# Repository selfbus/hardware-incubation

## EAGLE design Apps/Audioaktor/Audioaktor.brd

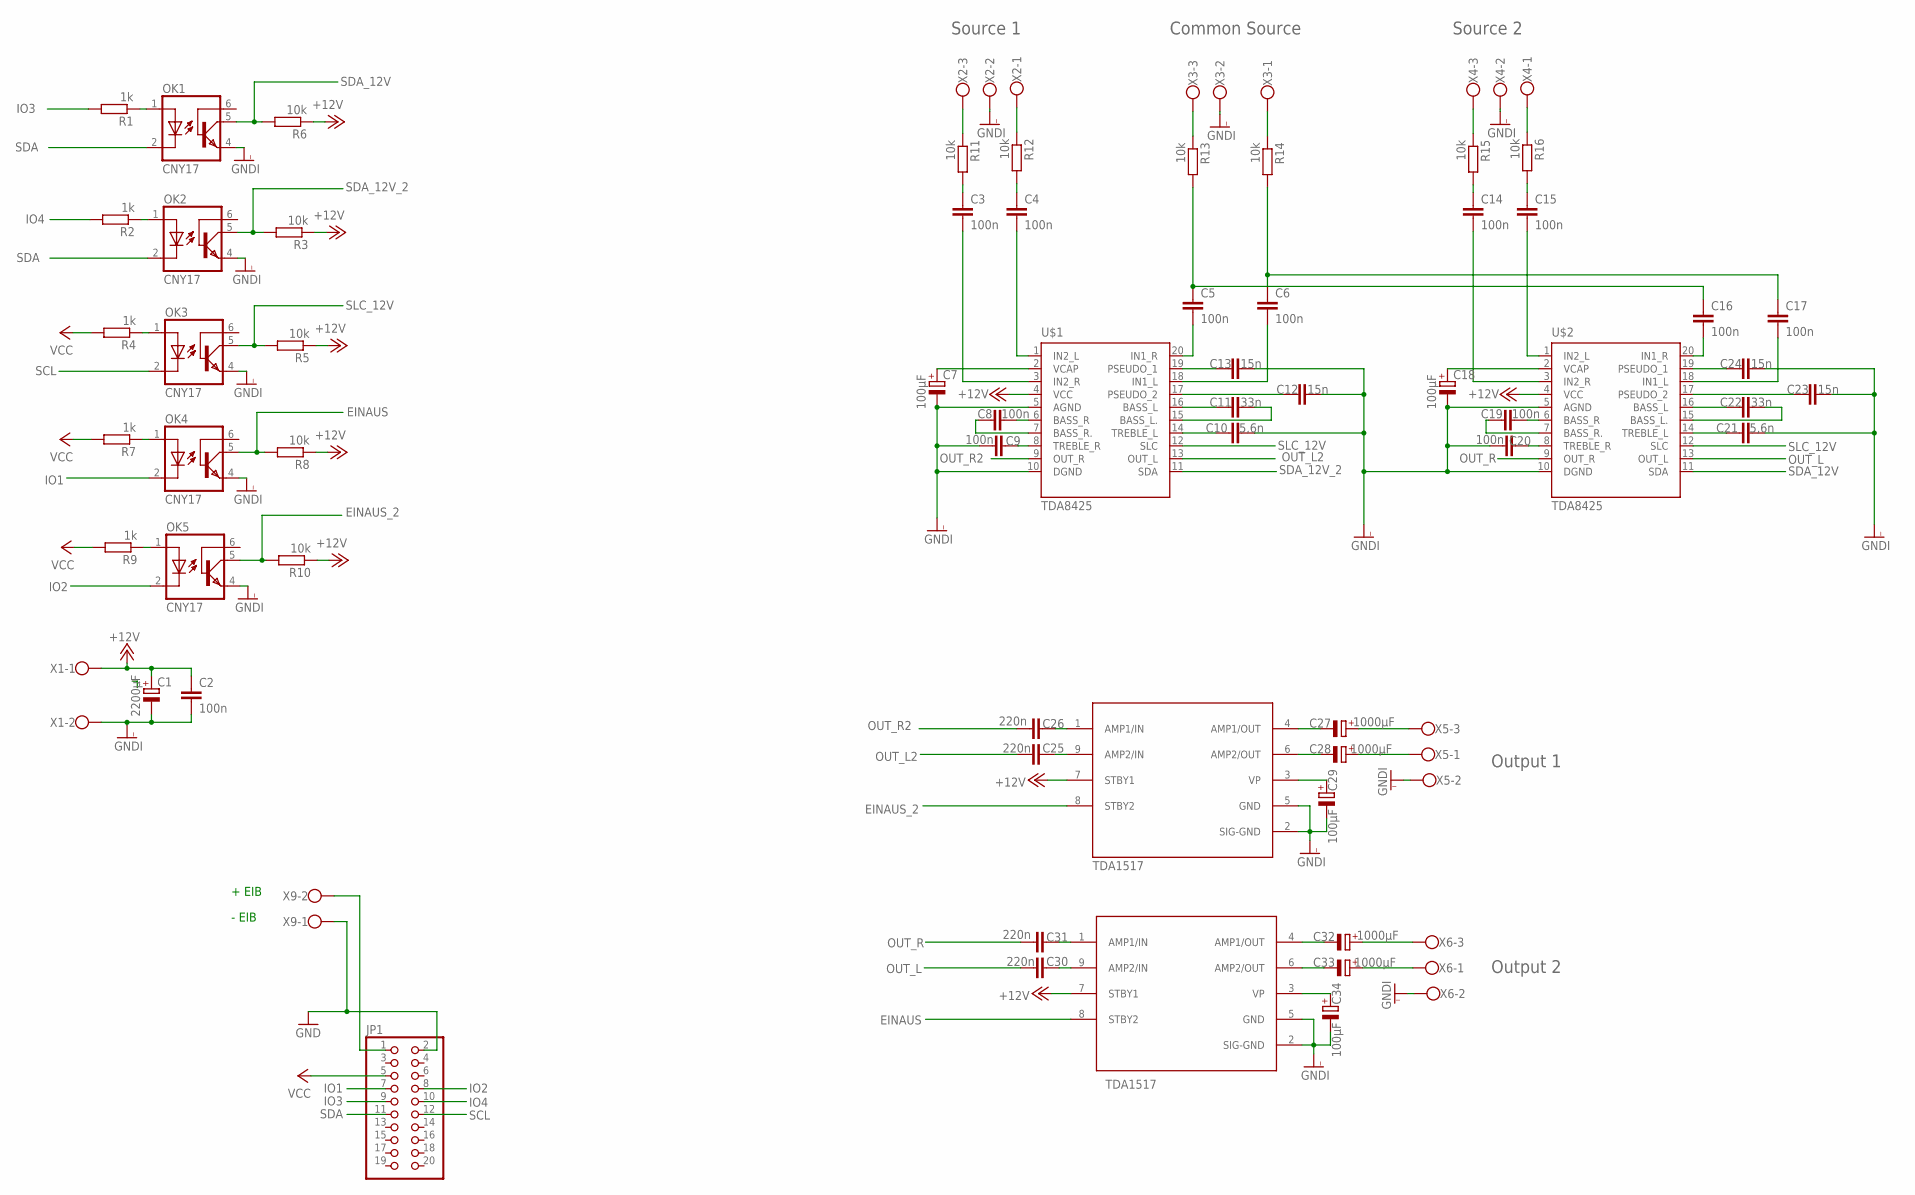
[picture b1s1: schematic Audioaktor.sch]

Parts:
C1: 2200µF; E5-10,5
C2, C3, C4, C5, C6, C8, C9, C14, C15, C16, C17, C19, C20: 100n; C050-030X075
C7, C18, C29, C34: 100µF; E5-10,5
C10, C21: 5,6n; C050-030X075
C11, C22: 33n; C050-030X075
C12, C13, C23, C24: 15n; C050-030X075
C25, C26, C30, C31: 220n; C050-030X075
C27, C28, C32, C33: 1000µF; E5-10,5
JP1: PINHD-2X10; 2X10
OK1, OK2, OK3, OK4, OK5: CNY17; DIL06
R1, R2, R4, R7, R9: 1k; 0204/7
R3, R5, R6, R8, R10, R11, R12, R13, R14, R15, R16: 10k; 0204/7
TDA1517: TDA1517
U$1, U$2: TDA8425; DIL20
U$3: TDA1517
X1, X9: W237-102
X2, X3, X4, X5, X6: W237-103

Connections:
+12V: C1.+, C2.1, R3.1, R5.1, R6.1, R8.1, R10.1, TDA1517.7 (STBY1), U$1.4 (VCC), U$2.4 (VCC), U$3.7 (STBY1), X1.1
EINAUS: OK4.5 (COL), R8.2, TDA1517.8 (STBY2)
EINAUS_2: OK5.5 (COL), R10.2, U$3.8 (STBY2)
GND: JP1.2, X9.1
GNDI: C1.-, C2.2, C7.-, C9.1, C10.2, C12.2, C13.2, C18.-, C20.1, C21.2, C23.2, C24.2, C29.-, C34.-, OK1.4 (EMI), OK2.4 (EMI), OK3.4 (EMI), OK4.4 (EMI), OK5.4 (EMI), TDA1517.2 (SIG-GND), TDA1517.5 (GND), U$1.5 (AGND), U$1.10 (DGND), U$2.5 (AGND), U$2.10 (DGND), U$3.2 (SIG-GND), U$3.5 (GND), X1.2, X2.2, X3.2, X4.2, X5.2, X6.2
IO1: JP1.7, OK4.2 (C)
IO2: JP1.8, OK5.2 (C)
IO3: JP1.9, R1.2
IO4: JP1.10, R2.2
unnamed: OK1.1 (A), R1.1
unnamed: OK2.1 (A), R2.1
unnamed: OK3.1 (A), R4.1
unnamed: OK4.1 (A), R7.1
unnamed: OK5.1 (A), R9.1
unnamed: R11.1, X2.3
unnamed: R12.1, X2.1
unnamed: C3.1, R11.2
unnamed: C4.1, R12.2
unnamed: R13.1, X3.3
unnamed: R14.1, X3.1
unnamed: C5.1, C16.1, R13.2
unnamed: C6.1, C17.1, R14.2
unnamed: C3.2, U$1.3 (IN2_R)
unnamed: C4.2, U$1.1 (IN2_L)
unnamed: C7.+, U$1.2 (VCAP)
unnamed: C8.2, U$1.6 (BASS_R)
unnamed: C8.1, U$1.7 (BASS_R.)
unnamed: JP1.1, X9.2
unnamed: C9.2, U$1.8 (TREBLE_R)
unnamed: C10.1, U$1.14 (TREBLE_L)
unnamed: C11.1, U$1.16 (BASS_L)
unnamed: C11.2, U$1.15 (BASS_L.)
unnamed: C13.1, U$1.19 (PSEUDO_1)
unnamed: C12.1, U$1.17 (PSEUDO_2)
unnamed: C5.2, U$1.20 (IN1_R)
unnamed: C6.2, U$1.18 (IN1_L)
unnamed: R15.1, X4.3
unnamed: R16.1, X4.1
unnamed: C14.1, R15.2
unnamed: C15.1, R16.2
unnamed: C26.2, U$3.1 (AMP1/IN)
unnamed: C25.2, U$3.9 (AMP2/IN)
unnamed: C27.-, U$3.4 (AMP1/OUT)
unnamed: C28.-, U$3.6 (AMP2/OUT)
unnamed: C14.2, U$2.3 (IN2_R)
unnamed: C15.2, U$2.1 (IN2_L)
unnamed: C18.+, U$2.2 (VCAP)
unnamed: C19.2, U$2.6 (BASS_R)
unnamed: C19.1, U$2.7 (BASS_R.)
unnamed: C20.2, U$2.8 (TREBLE_R)
unnamed: C21.1, U$2.14 (TREBLE_L)
unnamed: C22.1, U$2.16 (BASS_L)
unnamed: C22.2, U$2.15 (BASS_L.)
unnamed: C23.1, U$2.17 (PSEUDO_2)
unnamed: C24.1, U$2.19 (PSEUDO_1)
unnamed: C16.2, U$2.20 (IN1_R)
unnamed: C17.2, U$2.18 (IN1_L)
unnamed: C29.+, U$3.3 (VP)
unnamed: C31.2, TDA1517.1 (AMP1/IN)
unnamed: C27.+, X5.3
unnamed: C28.+, X5.1
unnamed: C30.2, TDA1517.9 (AMP2/IN)
unnamed: C32.-, TDA1517.4 (AMP1/OUT)
unnamed: C33.-, TDA1517.6 (AMP2/OUT)
unnamed: C34.+, TDA1517.3 (VP)
unnamed: C32.+, X6.3
unnamed: C33.+, X6.1
OUT_L: C30.1, U$2.13 (OUT_L)
OUT_L2: C25.1, U$1.13 (OUT_L)
OUT_R: C31.1, U$2.9 (OUT_R)
OUT_R2: C26.1, U$1.9 (OUT_R)
SCL: JP1.12, OK3.2 (C)
SDA: JP1.11, OK1.2 (C), OK2.2 (C)
SDA_12V: OK1.5 (COL), R6.2, U$2.11 (SDA)
SDA_12V_2: OK2.5 (COL), R3.2, U$1.11 (SDA)
SLC_12V: OK3.5 (COL), R5.2, U$1.12 (SLC), U$2.12 (SLC)
VCC: JP1.5, R4.2, R7.2, R9.2

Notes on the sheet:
+ EIB
- EIB
TDA1517
Source 1
Common Source
Source 2
Output 1
Output 2

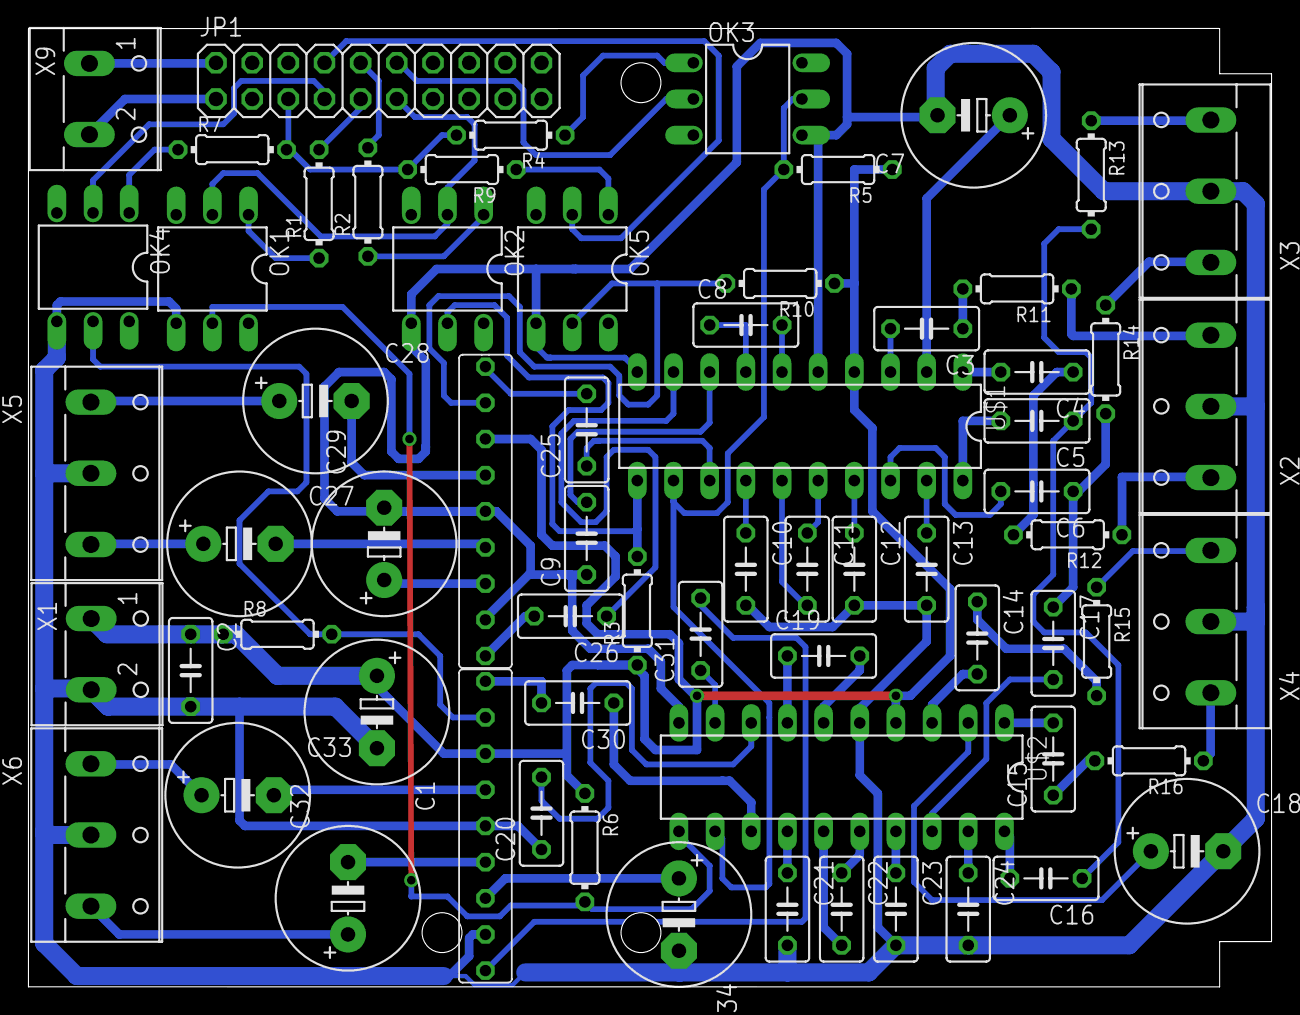
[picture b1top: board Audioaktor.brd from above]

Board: 2 copper layers, 87.3 x 67.3 mm, 67 parts (0 on the bottom side), 77 nets.

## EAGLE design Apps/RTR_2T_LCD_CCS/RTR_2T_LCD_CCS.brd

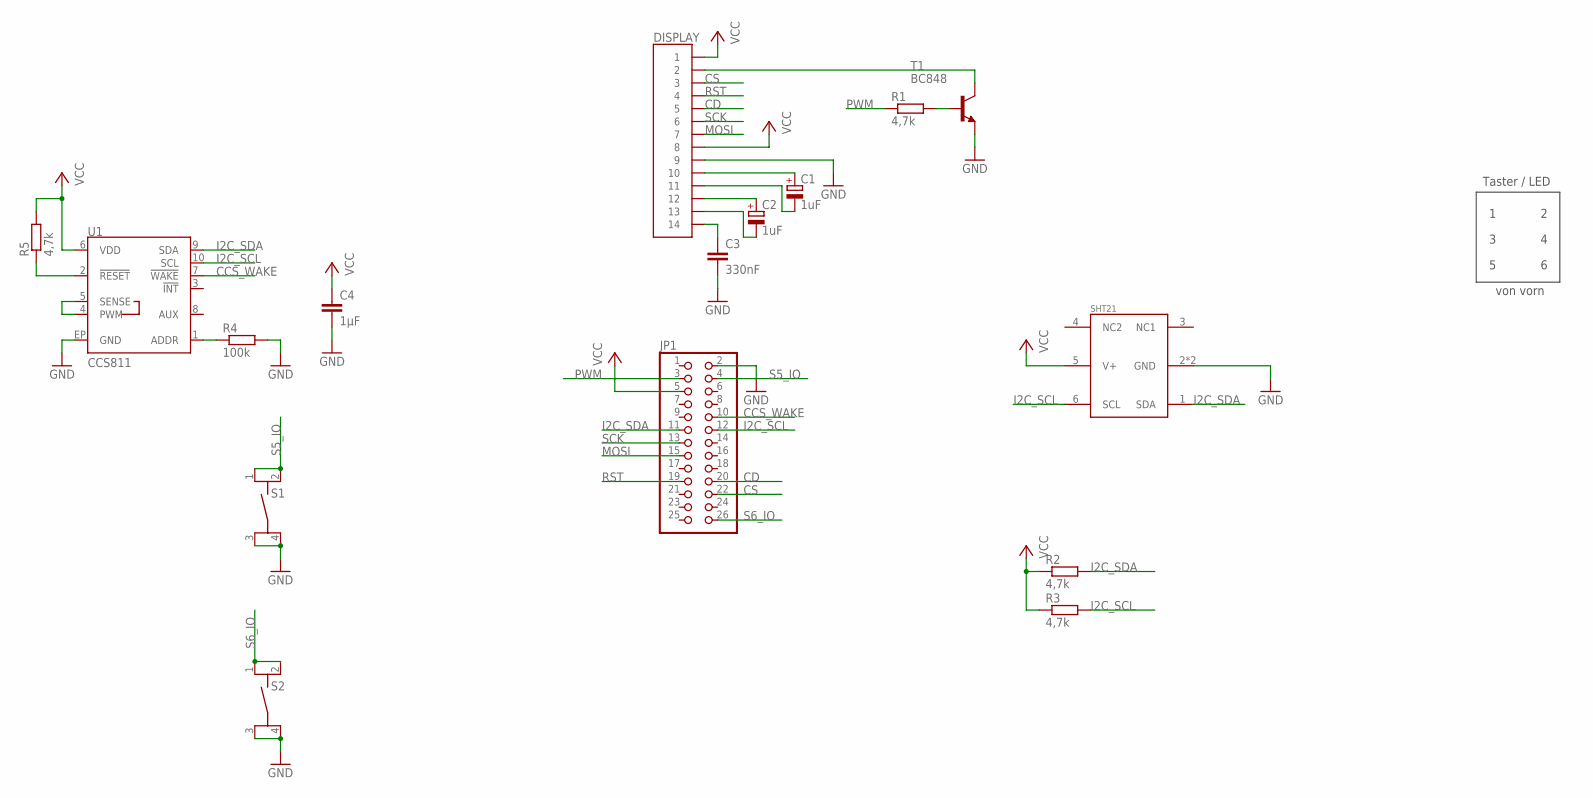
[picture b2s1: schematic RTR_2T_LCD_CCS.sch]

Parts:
C1, C2: 1uF; 153CLV-0405
C3: 330nF; C0805
C4: 1µF; C0805
DISPLAY: FFC-14; 14-POLIG
JP1: PINHD-2X13_2.54-SMD; 2X13SMD
R1, R2, R3, R5: 4,7k; R0805
R4: 100k; R0805
S1, S2: TASTER_9314SMD; TASTER_9314
SHT21: SHT21
T1: BC848; SOT23
U1: CCS811; LGA10

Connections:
CCS_WAKE: JP1.10, U1.7 (!WAKE!)
CD: DISPLAY.5, JP1.20
CS: DISPLAY.3, JP1.22
GND: C3.2, C4.2, DISPLAY.9, JP1.2, R4.2, S1.3, S1.4, S2.3, S2.4, SHT21.2 (GND), SHT21.P$1 (GND), T1.2 (E), U1.EP (GND)
I2C_SCL: JP1.12, R3.2, SHT21.6 (SCL), U1.10 (SCL)
I2C_SDA: JP1.11, R2.2, SHT21.1 (SDA), U1.9 (SDA)
MOSI: DISPLAY.7, JP1.15
unnamed: C1.+, DISPLAY.10
unnamed: C1.-, DISPLAY.11
unnamed: C2.+, DISPLAY.12
unnamed: C2.-, DISPLAY.13
unnamed: C3.1, DISPLAY.14
unnamed: U1.4 (PWM), U1.5 (SENSE)
unnamed: DISPLAY.2, T1.3 (C)
unnamed: R1.2, T1.1 (B)
unnamed: R4.1, U1.1 (ADDR)
unnamed: R5.1, U1.2 (!RESET!)
PWM: JP1.3, R1.1
RST: DISPLAY.4, JP1.19
S5_IO: JP1.4, S1.1, S1.2
S6_IO: JP1.26, S2.1, S2.2
SCK: DISPLAY.6, JP1.13
VCC: C4.1, DISPLAY.1, DISPLAY.8, JP1.5, R2.1, R3.1, R5.2, SHT21.5 (V+), U1.6 (VDD)

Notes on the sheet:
Taster / LED
von vorn

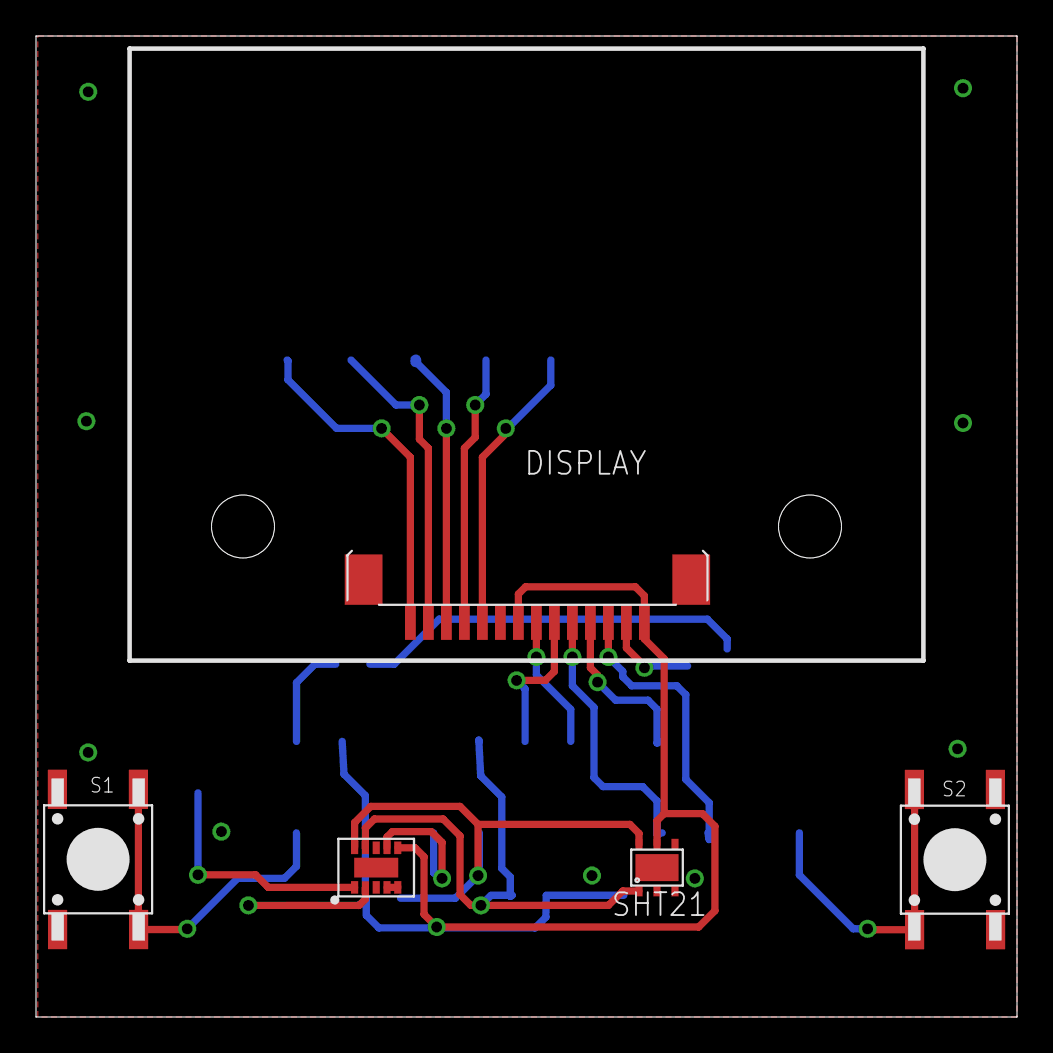
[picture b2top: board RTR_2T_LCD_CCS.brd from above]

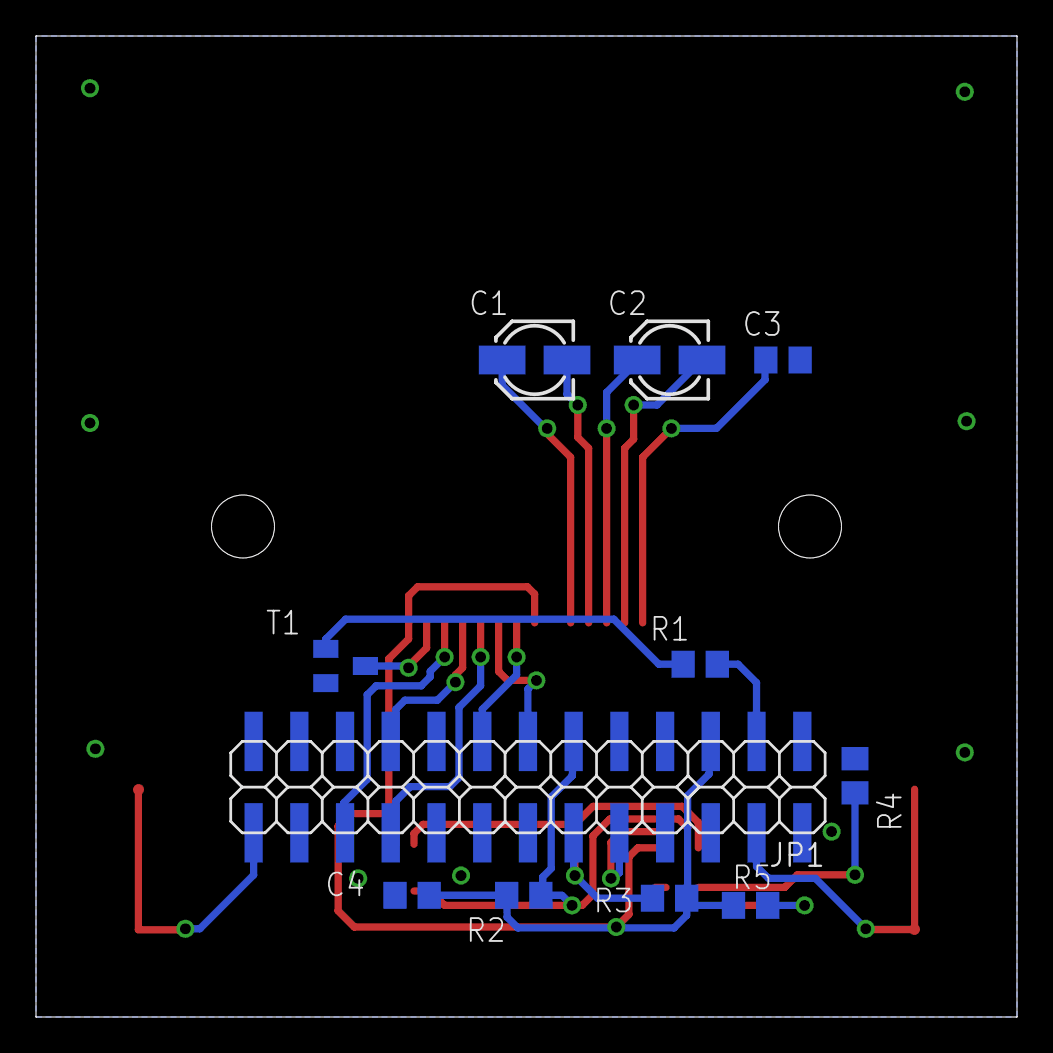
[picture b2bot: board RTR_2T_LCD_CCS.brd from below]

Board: 2 copper layers, 54.5 x 54.5 mm, 16 parts (11 on the bottom side), 23 nets.

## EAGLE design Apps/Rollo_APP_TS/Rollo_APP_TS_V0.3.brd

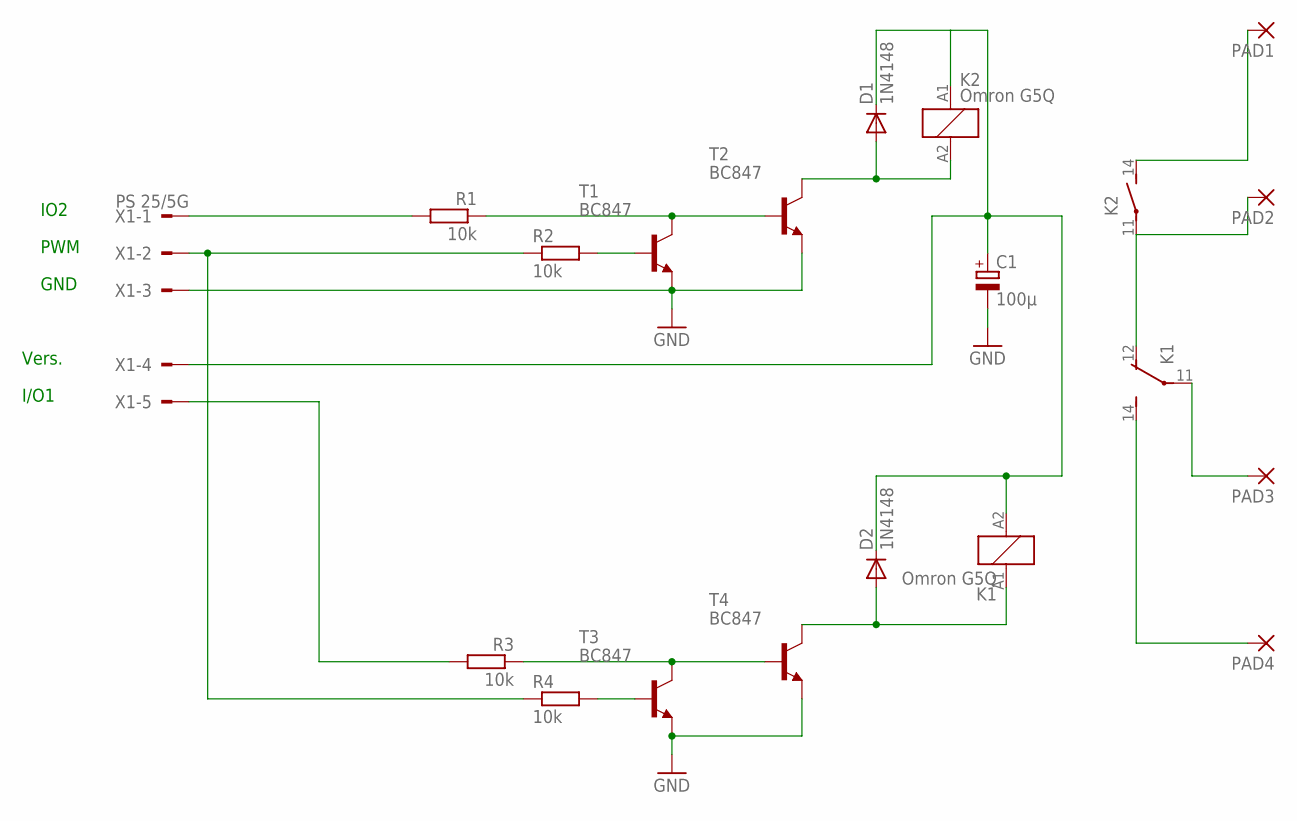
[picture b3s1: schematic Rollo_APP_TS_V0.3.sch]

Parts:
C1: 100µ; E3,5-8
D1, D2: 1N4148; MINIMELF
K1: Omron G5Q; FREEBUS_RELAY_G5Q_1_EU
K2: Omron G5Q; RE-SCHRACK
PAD1, PAD2, PAD3, PAD4: 3,81/1,4
R1, R2, R3, R4: 10k; M1206
T1, T2, T3, T4: BC847; SOT23
X1: PS 25/5G; 741256-49

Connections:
GND: C1.-, T1.2 (E), T2.2 (E), T3.2 (E), T4.2 (E), X1.3
unnamed: K1.12 (O), K2.11, PAD2.1
unnamed: R1.2, X1.1
unnamed: K2.14 (S), PAD1.1
unnamed: R3.2, X1.5
unnamed: K1.14 (S), PAD4.1
unnamed: K1.11, PAD3.1
unnamed: R2.1, R4.1, X1.2
unnamed: R3.1, T3.3 (C), T4.1 (B)
unnamed: R4.2, T3.1 (B)
unnamed: R1.1, T1.3 (C), T2.1 (B)
unnamed: R2.2, T1.1 (B)
R1: D2.A, K1.A1 (1), T4.3 (C)
R3: D1.A, K2.A2 (2), T2.3 (C)
VDD_IN1: C1.+, D1.C, D2.C, K1.A2 (2), K2.A1 (1), X1.4

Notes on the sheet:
PWM
I/O1
GND
IO2
Vers.

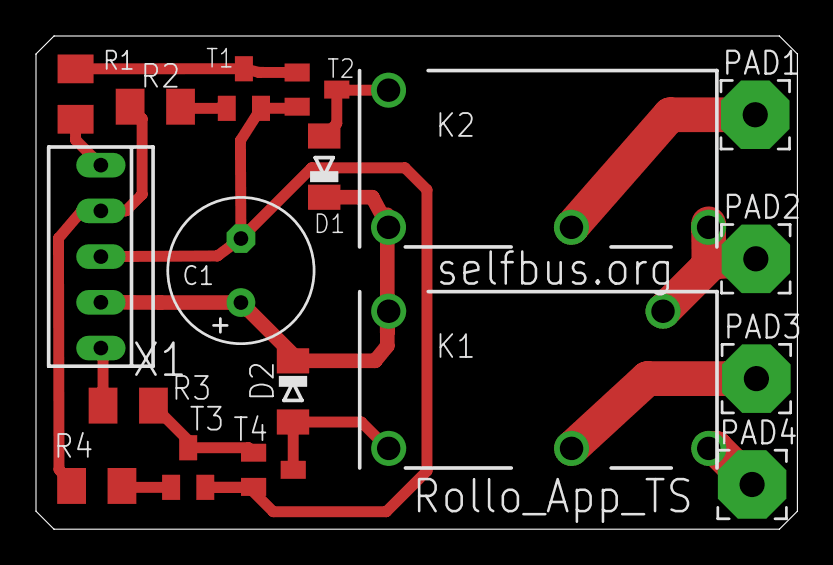
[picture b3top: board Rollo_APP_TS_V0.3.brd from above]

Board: 2 copper layers, 42.3 x 27.4 mm, 18 parts (0 on the bottom side), 15 nets.
